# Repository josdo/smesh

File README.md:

# What is SMesh?
SMesh is a sensor mesh network ("smesh") that performs long duration environmental sensing for sustainability research at Stanford.

A smesh node (or "snode") consists of a sensor payload plus a Meshtastic board that can relay readings using long range LoRa radio.

# Usage
`snode` is a Python package that contains all dependencies and code to read from snodes.

Files are organized into three directories:
1. One-off scripts go into `snode/scripts`
2. Reusable code that scripts can import go into `snode/snode`
3. Tests for reusable code go into `snode/tests`

To run any Python code:
1. Install Poetry by following https://python-poetry.org/docs/#installing-with-pipx
2. Enter the package you're using, e.g., `cd snode`
3. Install the Python dependencies the code needs, i.e., `poetry install`
4. Run a Python script, i.e., `poetry run python PATH/TO/SCRIPT.PY`

# Customizing Meshtastic firmware
Snodes run a stable version of Meshtastic firmware with small modifications.

To access this firmware:
1. Clone the firmware fork, i.e. `git clone https://github.com/josdo/meshtastic-firmware.git`
2. Follow https://meshtastic.org/docs/development/firmware/build/ to set up PlatformIO, a tool to build firmware from source. 
   **Note:** at step 3, pick `heltec-v3` from the list of options given.

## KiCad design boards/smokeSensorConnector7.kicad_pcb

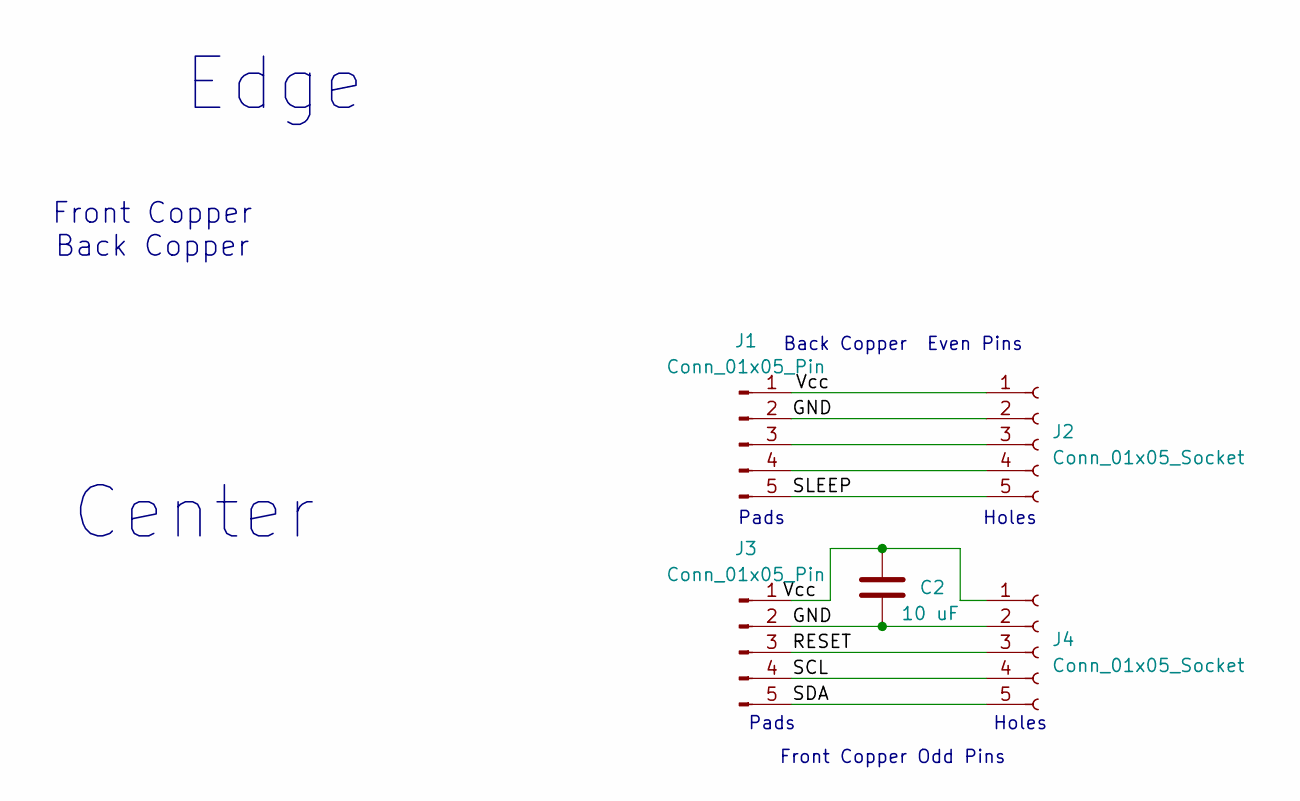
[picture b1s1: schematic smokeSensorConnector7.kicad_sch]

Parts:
C2: 10 uF; C_0805_2012Metric_Pad1.18x1.45mm_HandSolder
J1, J3: Conn_01x05_Pin; PinHeader_2x05_P1.00mm_Vertical_SMD
J2, J4: Conn_01x05_Socket; PinSocket_1x05_P2.54mm_Vertical

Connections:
/GND: C2.2, J1.2, J2.2, J3.2, J4.2
/RESET: J3.3, J4.3
/SCL: J3.4, J4.4
/SDA: J3.5, J4.5
/SLEEP: J1.5, J2.5
/Vcc: C2.1, J1.1, J2.1, J3.1, J4.1
unnamed: J1.3, J2.3
unnamed: J1.4, J2.4

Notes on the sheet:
Front Copper Back Copper
Center
Front Copper Odd Pins
Back Copper Even Pins
Pads Holes
Edge

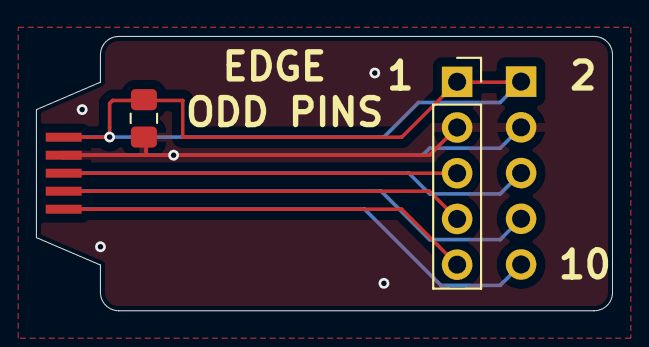
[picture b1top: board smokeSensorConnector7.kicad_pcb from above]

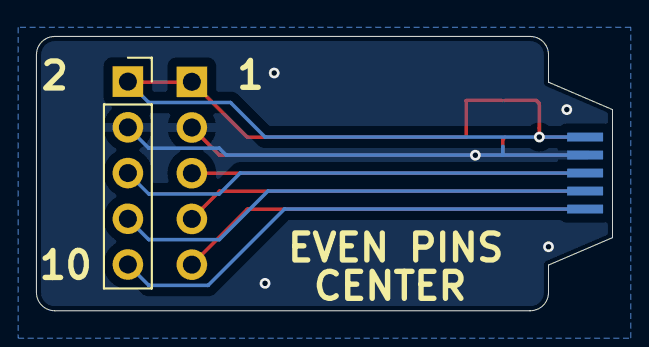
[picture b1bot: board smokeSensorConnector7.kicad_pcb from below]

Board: 2 copper layers, 32.0 x 15.2 mm, 5 parts (2 on the bottom side), 8 nets.

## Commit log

2024-08-14 Initialize repo.
2024-08-17 Read sensor data from serial port.
2024-08-17 Fix reading script.
2024-08-23 Improve readings script.
2024-08-23 Read INA260 current readings.
2024-08-27 Change packet fromId to packet from for more accurate node info
2024-08-29 Add sensor logging and traceroute script
2024-08-31 Update new log readings from second Jasper Ridge trip
2024-08-31 Add Packard log readings
2024-09-03 Move metrics to data folder
2024-09-03 Move w6yx data
2024-09-07 Update data 9/7/24
2024-09-07 Add w6yx data 9/7/24
2024-09-15 w6yx data update 9/15/24
2024-09-21 update logged readings 9/21/24
2024-09-23 update data log after beta jr (fbec) added to jasper ridge
2024-09-23 update data
2024-09-28 update data 9/28/24
2024-09-28 uploaded smoke sensor pcb and stl files for antenna holder
2024-09-28 Read first part of meshtastic --info into a json.
2024-09-28 Rename file.
2024-09-28 Read all info into json.
    * TODO: verify values correctly
2024-09-28 Simple updates for ReadMe clarity
2024-10-08 Handling of incomplete data stream
2024-10-08 Checked with current 62e4
2024-10-12 add demo 0098
2024-10-12 add demo 0098 config info
2024-10-12 flash all smesh configurations
2024-10-20 Testing 4 Snodes and 1 logger in Lab64 for sensor transmission and channel utilization on Sunday 10/20/24
2024-11-07 Node communication visualization code
